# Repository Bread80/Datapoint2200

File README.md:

# Datapoint 2200 Schematics, Documents and PCB Recreations (WiP)

This is my project to transcribe the schematics for a Datapoint 2200 serial processor machine, reverse engineer them, and recreate the original hardware with added blinkenlights.

The repository contains schematics, PCB layout files, documents and software relevant to the 2200.

The schematics are in Kicad 5 format (at least until I make my peace with the UI in newer versions). To open them you may need to import the symbol library in Datapoint2200.lib and the Datapoint2200.pretty folder.

NOTES:
* These documents are still a work in progress.
* Schematics have not been double checked or verified against original hardware.
* On the original schematics some of the connector pinouts are ambiguous. DO NOT rely on the data in this repository when working with original hardware.

## Files
Some of the included files/PDFs:
* 2200_Drawing_package.pdf - Original schematics and engineering drawings.
* 2200_Reference_Manual.pdf - The operating manual for the machine including the assembly instruction set.
* 2200_Programmers_Man_Aug71.pdf - The processor instruction set, description of the standard libraries and operating instructions for the operating system, editor and assembler. Also contains a source code listing of the operating system software (but not the libraries, assembler or editor).
* 1405_Shift_Memory.pdf - Datasheet for the shift memory used in processor and video display.
* 74LS189_FairchildSemiconductor.pdf - Datasheet for the memory ICs used to implement the processor stack. (Which actually used very similiar 7489 ICs. The recreation has been designed to be able to use either).
* 1982_Standard_Microsystems.pdf - A datasheet catalogue which includes that for a character ROM compatible with one of those used in the video display, including character bitmaps.
* Datapoint2200.lib and .dcm - Kicab custom symbols (for Kicad 5).
* InstructionSet.txt - The instruction sets for both versions of the 2200 and the (very similar) Intel 8008.
* InstructionSet.xlsx - Spreadsheet version of the instruction sets (2200 and 8008) including comparisons against the Z80/8080.

## Folders/Boards
Schematics for each board are in their own folder.

The following lists the key boards of the Datapoint 2200 and the current status of each board.

### Board A1: Power Supply, Regulator
Status: Not transcribed.

### Board A2: Modulator
Modulator for the tape drives

Status: Not transcribed yet.

### Board A3: Demodulator
Demodulator for the tape drives

Status: Not transcribed yet.

### Board A4: Decoder
The system sequencer and output port/command decoder.

The schematic is split into the following files and functional units:
* Scheduler: Contains the system clock and gneerates signals to control the processort and machine as a whole.
* IODecoder: Decodes output port (command) addresses into individual signal lines.
* Speaker_Tape: Generates sound to the speaker (beeps and clicks), and houses some gates spilled over from the tape drive boards.

Status: A first revision board has been manufactured and works but has a couple of largely cosmetic issues, the worst of which is an incorrect footprint for the wide-body TTL chips. The PCB currently in the repository is the proposed next revision but which has not been tested - I'll have it manufactured when I know it is driving the rest of the system correctly.

### Board A5: Processor
---
The processor itself. The schematic is divided up as follows:
* AddressRegister: The address register (counter).
* AddrRegAndStackControl: Controls reading data into the address register and program counter, incrementing the program counter, and the stack.
* ALU: The ALU and carry flag.
* ARegister: The A register and I/O bus.
* Flags: The flags (other than carry) and conditional jump/call/return handling.
* InstrDecdoing: Instruction decoding.
* IRegister: The instruction register and register decoding.
* Processor: The main overview.
* Registers1: The H and L registers and data bus logic.
* Registers2: The B, C, D and E registers.
* Stack: The stack and stack pointer, and memory card selection.
* Timing: Fetch-execute cycle, memory word sync, HALTing and running, clocking and miscellaneous.

Status: The design has been tested in a logic emulator and appears to function correctly. A PCB layout has been made up and I'm currently adding LEDs (and establishing which signals should have LEDs) before sending the board for production.

### Board A6: Keyboard
---
Houses the keyswitches and multiplexing circuitry.

Status: Transcribed but not checked.

### Board A7: Deflection Amplifier
---
This board houses the circuitry for driving the CRT, and also some TTL logic spilled over from the Display Control board.

Status: The TTL circuits have been transcribed. I'm proposing to replace the CRT circuitry with something capable of driving a suitable modern display (ie. something microcontroller based).

### Board A8: Display Control
The 'video card'. Contains video memory, character generator and display driver. The board also controls the reading of data from the keyboard.

The schematic is divided as follows
* Input: I/O decoder for the display and keyboard (they use the same port address) and controls the latching of video data (control register, horizontal and vertical position and data).
* Memory: Video memory (using 1405 shift registers).
* Pixel Gen: Pixel clock, 'diddle scanning' (row and column wthin each character), characters ROMs and cursor generation.
* RowColumnSync: Row and column scanning and latches, and syncing the two for writing video data to memory.
* ClearAndOutput: Clearing memory for to-end-of-row, to-end-of-screen and clear-display functions. Outputting the status register (display busy and keyboard mounted switches).

Status: Transcribed and checked (but not validated).

### Board A9: Keyboard Logic
Contains the logic for scanning the keyboard, latching returned keypresses, and outputting characted codes in ASCII.

Contains the following modules:
* Reboot: Drives the processor after rebooting to load the boot data from a tape drive.
* ReadControl: Controls the processor's input bus. The board either outputs data from the keyboard itself or the bus buffers(probably).
* 'Sheet1': The main keyboard scanning and latching circuit. This name is probably not optimal.
* Shift: A circuit spilled opver from 'Sheet1' which controls 'shifting' of ASCII codes.
* BusBuffers: Comparators to boost the signals from the external bus and forward them to the processor's input bus.
* RunSwitch: A small circuit to latch the state of the Run switch.

Status: Transcribed and checked but not validated.

### Boards A11 to A14: Memory cards
Houses the Intel 1405 shift memories ICs used by the processor and related row and column decoders.

Status: Transcribed and first revision boards manufactured. The recreated PCBs include solder links to enable the memory to be operated at TTL voltage levels.
Note: The board has not been tested with actual 1405 chips.
Note: The 1405 ICs require a lot of power. The original PCBs are heavily engineered to be able to supply this power, and include a pair of bus bars for power distribution. The recreated PCBs have not been engineered to the same standards and shift should *not* be used with shift memories.

### Board A17: Motherboard
The 'backplane' into which many of the above boards slot (A1 to A9 except A6) or connect.

Status: Not transcribed yet

(Other board numbers are for smaller boards such as those in the tape machines, speaker mountings etc).

## Other Repository Contents
* Egde56: A test for for attaching to an edge connector.
* Software: A transcription and binaries for the operating system software listed in the Programmers Manual.

## Design Standards
These are mainly notes for myself to keep things consistent between boards.
  
Components:
  LEDs, side facing: Datapoint2200:LED_Dialight_597_xxxx_407F_SMT_RA_3mmx2mmx1mm (custom component and footprint in Datapoint2200 library)

Footprints:
Decoupling capacitors: Capacitor_THT:C_Disc_D7.0mm_W2.5mm_P5.00mm
Resistors (through hole): Resistor_THT:R_Axial_DIN0207_L6.3mm_D2.5mm_P10.16mm_Horizontal
Resistors (surface mount): 
  Decoder uses 0805: Resistor_SMD:R_0805_2012Metric_Pad1.20x1.40mm_HandSolder
  (other boards will vary!)
Mounting holes: MountingHole:MountingHole_3.2mm_M3
  Holes positioned 7x 25mils from board edges
Buttons (side mounted): Button_Switch_THT:SW_Tactile_SPST_Angled_PTS645Vx58-2LFS (exact model to be clarified)

Silkscreen:
All silkscreen placed on a 25mil (0.6250mm) grid
Section titles font size: W1.5 H1.5 Thickness: .25
Text for ICs:
  Top left: chip code (e.g. 7493), stated with original 74 series (no LS, HCT etc)
  Top right: reference code (e.g Z19)
  Below: chip description, centred. Use summary from datasheet where possible
Text for edge connector pins:
  Left (right on reverse) aligned to edge connector
  Use a < or > at connector end to indicate signal direction
  Positioned 50mil (2x0.6350mm) from connector pad
Edge connector pin numbers:
  Label first and last pin on each side.
  Font size: H1.5 H1.5 Thickness: 0.25
  Position: centred aligned
    8x 25mil horizontally from edge of connector pads
	4x 25mil vertically from centre of first pad
Board identifier (e.g. A4)
  Font size: H2 W2 Thickness: 0.35, orientation 90 degrees (i.e. from bottom to top) (Orientation valid for 'main' PCBs)
  Positioning: Centre aligned, 6x 25mils from board edge, 6x 25mils from edge of edge connector
Lines:
  Section separators: 0.5mm width
  Sub-section separators: 0.12mm width

*74x00	4	quad 2-input NAND gate			14	SN74LS00
*74x02	4	quad 2-input NOR gate			14	SN74LS02
*74x03	4	quad 2-input NAND gate		open-collector	14	SN74LS03
*74x04	6	hex inverter gate			14	SN74LS04
*74x05	6	hex inverter gate		open-collector	14	SN74LS05
**74x06	6	hex inverter gate		open-collector 30 V / 40 mA	14
*74x08	4	quad 2-input AND gate			14	SN74LS08
*74x10	3	triple 3-input NAND gate			14	SN74LS10
*74x20	2	dual 4-input NAND gate			14	SN74LS20
*74x30	1	single 8-input NAND gate			14	SN74LS30
**74x37	4	quad 2-input NAND gate		driver NO=30	14	SN74LS37
**74x40	2	dual 4-input NAND gate		driver NO=30	14	SN74LS40
*74x42	1	BCD to decimal decoder			16	SN74LS42
*74x73	2	dual J-K flip-flop, asynchronous clear			14	SN54LS73A
*74x74	2	dual D positive edge triggered flip-flop, asynchronous preset and clear			14	SN74LS74A
*74x85	1	4-bit magnitude comparator			16	SN74LS85
*74x89	1	64-bit RAM (16x4), 4 data inputs, 4 inverted data outputs		open-collector	16	SN7489
*74x95	1	4-bit shift register, parallel in, parallel out, serial input; different pinout for 74L95			14
*74x151	1	8-line to 1-line data selector/multiplexer			16	SN74151A
*74x153	2	dual 4-line to 1-line data selector/multiplexer, non-inverting outputs			16	SN74153
*74x164	1	8-bit serial-in parallel-out (SIPO) shift register, asynchronous clear, not output latch			14	SN74164
*74x193	1	synchronous presettable up/down 4-bit binary counter, clear			16	SN74193

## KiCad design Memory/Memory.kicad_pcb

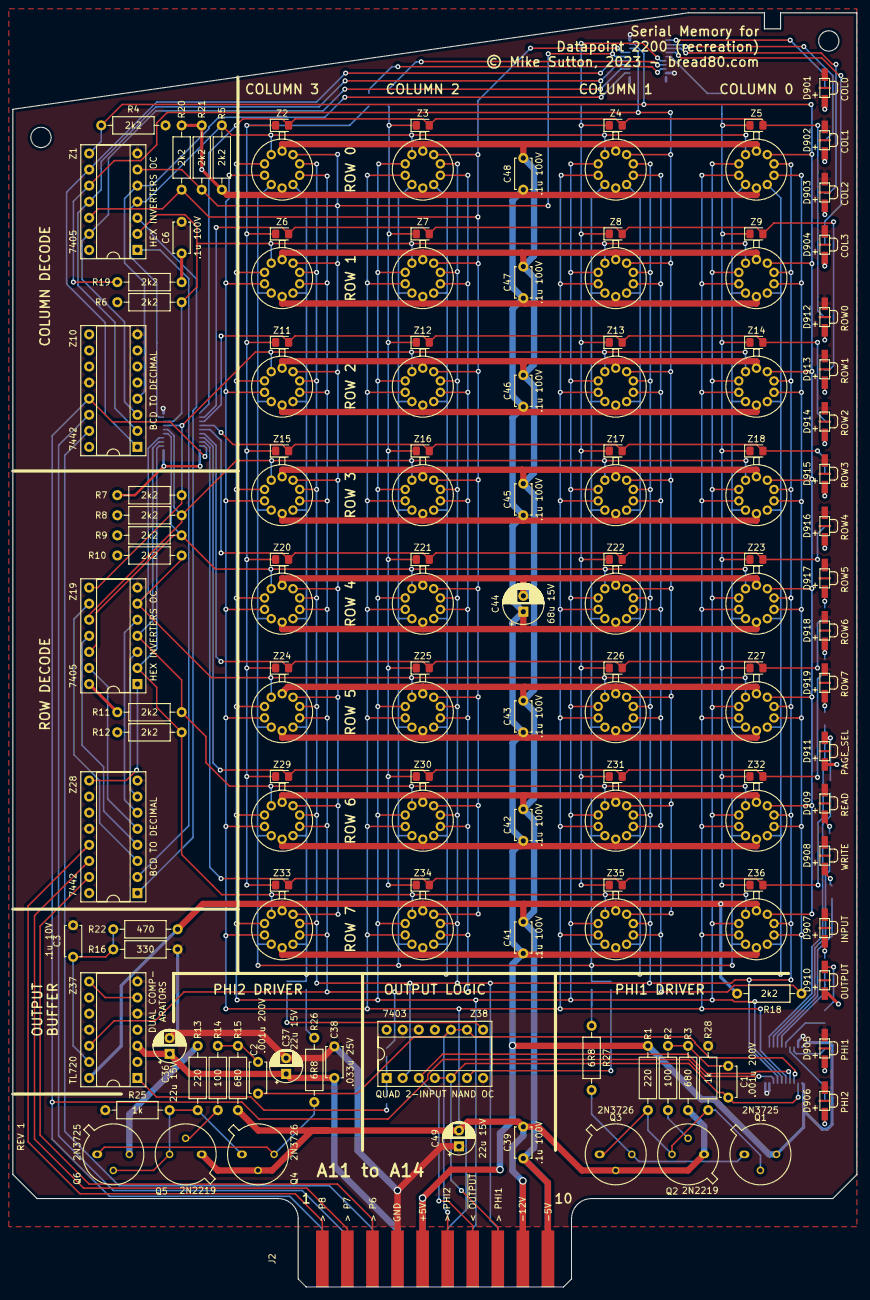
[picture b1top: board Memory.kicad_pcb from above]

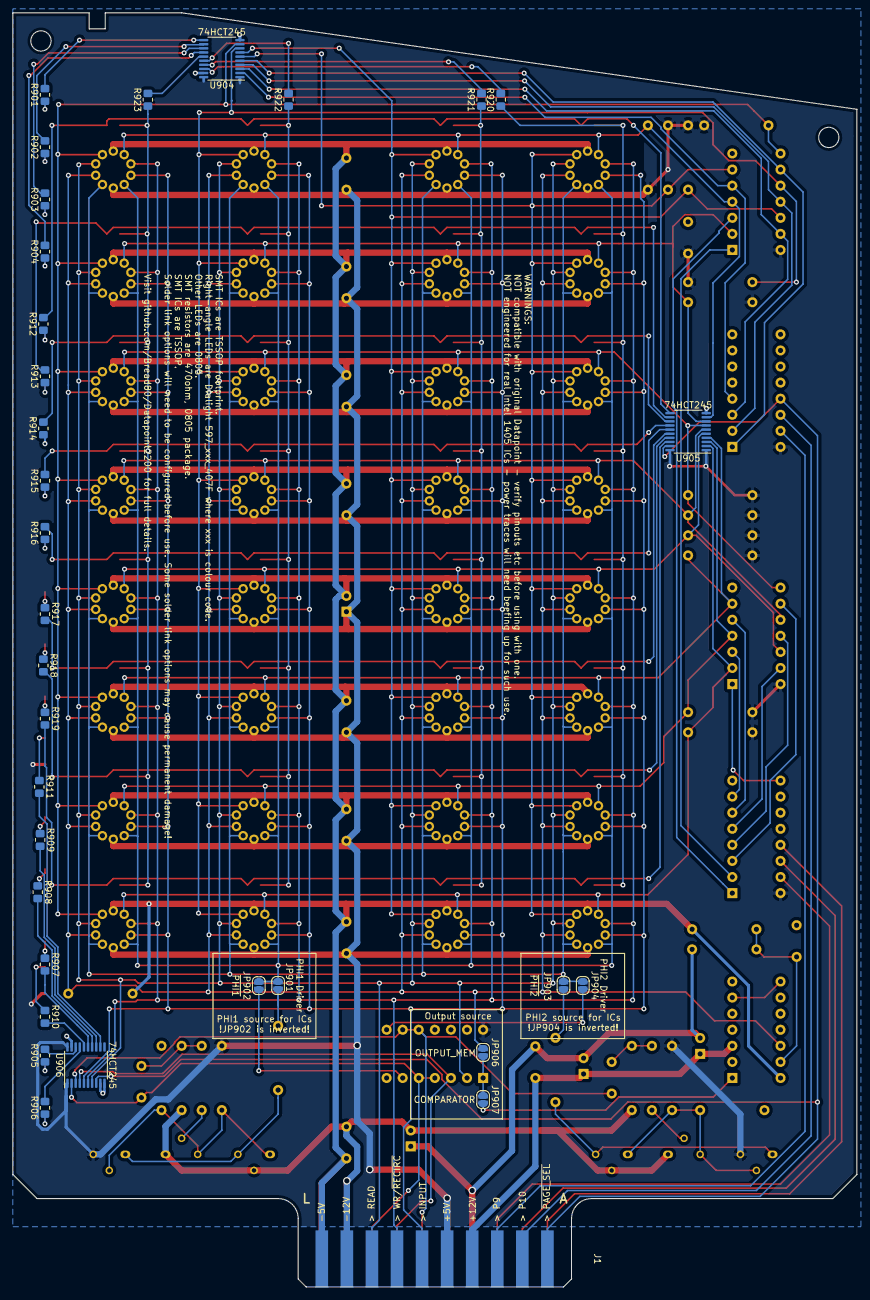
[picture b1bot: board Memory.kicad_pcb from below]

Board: 2 copper layers, 133.3 x 201.3 mm, 173 parts (33 on the bottom side), 106 nets.

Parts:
C1, C2: .001u 200V; C_Disc_D4.7mm_W2.5mm_P5.00mm
C3: .1u 10V; C_Disc_D4.7mm_W2.5mm_P5.00mm
C6, C39, C41, C42, C43, C45, C46, C47, C48: .1u 100V; C_Disc_D4.7mm_W2.5mm_P5.00mm
C36, C37, C49: 22u 15V; CP_Radial_D5.0mm_P2.50mm
C38: .033u 25V; C_Disc_D4.7mm_W2.5mm_P5.00mm
C44: 68u 15V; CP_Radial_D6.3mm_P2.50mm
D901: COL0; LED_Dialight_597_xxxx_407F_SMT_RA_3mmx2mmx1mm
D902: COL1; LED_Dialight_597_xxxx_407F_SMT_RA_3mmx2mmx1mm
D903: COL2; LED_Dialight_597_xxxx_407F_SMT_RA_3mmx2mmx1mm
D904: COL3; LED_Dialight_597_xxxx_407F_SMT_RA_3mmx2mmx1mm
D905: PHI1; LED_Dialight_597_xxxx_407F_SMT_RA_3mmx2mmx1mm
D906: PHI2; LED_Dialight_597_xxxx_407F_SMT_RA_3mmx2mmx1mm
D907: INPUT; LED_Dialight_597_xxxx_407F_SMT_RA_3mmx2mmx1mm
D908: WRITE; LED_Dialight_597_xxxx_407F_SMT_RA_3mmx2mmx1mm
D909: READ; LED_Dialight_597_xxxx_407F_SMT_RA_3mmx2mmx1mm
D910: OUTPUT; LED_Dialight_597_xxxx_407F_SMT_RA_3mmx2mmx1mm
D911: PAGE_SEL; LED_Dialight_597_xxxx_407F_SMT_RA_3mmx2mmx1mm
D912: ROW0; LED_Dialight_597_xxxx_407F_SMT_RA_3mmx2mmx1mm
D913: ROW1; LED_Dialight_597_xxxx_407F_SMT_RA_3mmx2mmx1mm
D914: ROW2; LED_Dialight_597_xxxx_407F_SMT_RA_3mmx2mmx1mm
D915: ROW3; LED_Dialight_597_xxxx_407F_SMT_RA_3mmx2mmx1mm
D916: ROW4; LED_Dialight_597_xxxx_407F_SMT_RA_3mmx2mmx1mm
D917: ROW5; LED_Dialight_597_xxxx_407F_SMT_RA_3mmx2mmx1mm
D918: ROW6; LED_Dialight_597_xxxx_407F_SMT_RA_3mmx2mmx1mm
D919: ROW7; LED_Dialight_597_xxxx_407F_SMT_RA_3mmx2mmx1mm
D920: Z5; LED_0805_2012Metric_Pad1.15x1.40mm_HandSolder
D921: Z4; LED_0805_2012Metric_Pad1.15x1.40mm_HandSolder
D922: Z3; LED_0805_2012Metric_Pad1.15x1.40mm_HandSolder
D923: Z2; LED_0805_2012Metric_Pad1.15x1.40mm_HandSolder
D924: Z9; LED_0805_2012Metric_Pad1.15x1.40mm_HandSolder
D925: Z8; LED_0805_2012Metric_Pad1.15x1.40mm_HandSolder
D926: Z7; LED_0805_2012Metric_Pad1.15x1.40mm_HandSolder
D927: Z6; LED_0805_2012Metric_Pad1.15x1.40mm_HandSolder
D928: Z14; LED_0805_2012Metric_Pad1.15x1.40mm_HandSolder
D929: Z13; LED_0805_2012Metric_Pad1.15x1.40mm_HandSolder
D930: Z12; LED_0805_2012Metric_Pad1.15x1.40mm_HandSolder
D931: Z11; LED_0805_2012Metric_Pad1.15x1.40mm_HandSolder
D932: Z18; LED_0805_2012Metric_Pad1.15x1.40mm_HandSolder
D933: Z17; LED_0805_2012Metric_Pad1.15x1.40mm_HandSolder
D934: Z16; LED_0805_2012Metric_Pad1.15x1.40mm_HandSolder
D935: Z15; LED_0805_2012Metric_Pad1.15x1.40mm_HandSolder
D936: Z23; LED_0805_2012Metric_Pad1.15x1.40mm_HandSolder
D937: Z22; LED_0805_2012Metric_Pad1.15x1.40mm_HandSolder
D938: Z21; LED_0805_2012Metric_Pad1.15x1.40mm_HandSolder
D939: Z20; LED_0805_2012Metric_Pad1.15x1.40mm_HandSolder
D940: Z27; LED_0805_2012Metric_Pad1.15x1.40mm_HandSolder
D941: Z26; LED_0805_2012Metric_Pad1.15x1.40mm_HandSolder
D942: Z25; LED_0805_2012Metric_Pad1.15x1.40mm_HandSolder
D943: Z24; LED_0805_2012Metric_Pad1.15x1.40mm_HandSolder
D944: Z32; LED_0805_2012Metric_Pad1.15x1.40mm_HandSolder
D945: Z31; LED_0805_2012Metric_Pad1.15x1.40mm_HandSolder
D946: Z30; LED_0805_2012Metric_Pad1.15x1.40mm_HandSolder
D947: Z29; LED_0805_2012Metric_Pad1.15x1.40mm_HandSolder
D948: Z36; LED_0805_2012Metric_Pad1.15x1.40mm_HandSolder
D949: Z35; LED_0805_2012Metric_Pad1.15x1.40mm_HandSolder
D950: Z34; LED_0805_2012Metric_Pad1.15x1.40mm_HandSolder
D951: Z33; LED_0805_2012Metric_Pad1.15x1.40mm_HandSolder
H901, H902: MountingHole; MountingHole_3.2mm_M3
J1: Edge_Bottom; EdgeConn_10_Pin_Pitch_3.96mm
J2: Edge_Top; EdgeConn_10_Pin_Pitch_3.96mm
JP901: PHI1 Driver; SolderJumper-2_P1.3mm_Open_RoundedPad1.0x1.5mm
JP902: ~PHI1; SolderJumper-2_P1.3mm_Open_RoundedPad1.0x1.5mm
JP903: PHI2 Driver; SolderJumper-2_P1.3mm_Open_RoundedPad1.0x1.5mm
JP904: ~PHI2; SolderJumper-2_P1.3mm_Open_RoundedPad1.0x1.5mm
JP906: OUTPUT_MEM; SolderJumper-2_P1.3mm_Open_RoundedPad1.0x1.5mm
JP907: COMPARATOR; SolderJumper-2_P1.3mm_Open_RoundedPad1.0x1.5mm
Q1, Q6: 2N3725; TO-39-3
Q2, Q5: 2N2219; TO-39-3
Q3, Q4: 2N3726; TO-39-3
R1, R13: 220; R_Axial_DIN0207_L6.3mm_D2.5mm_P10.16mm_Horizontal
R2, R14: 100; R_Axial_DIN0207_L6.3mm_D2.5mm_P10.16mm_Horizontal
R3, R15: 680; R_Axial_DIN0207_L6.3mm_D2.5mm_P10.16mm_Horizontal
R4, R5, R6, R7, R8, R9, R10, R11, R12, R18, R19, R20, R21: 2k2; R_Axial_DIN0207_L6.3mm_D2.5mm_P10.16mm_Horizontal
R16: 330; R_Axial_DIN0207_L6.3mm_D2.5mm_P10.16mm_Horizontal
R22: 470; R_Axial_DIN0207_L6.3mm_D2.5mm_P10.16mm_Horizontal
R25, R28: 1k; R_Axial_DIN0207_L6.3mm_D2.5mm_P10.16mm_Horizontal
R26, R27: 6R8; R_Axial_DIN0207_L6.3mm_D2.5mm_P10.16mm_Horizontal
R901, R902, R903, R904, R905, R906, R907, R908, R909, R910, R911, R912, R913, R914, R915, R916, R917, R918, R919, R920, R921, R922, R923: 470R; R_0805_2012Metric_Pad1.20x1.40mm_HandSolder
U904, U905, U906: 74HCT245; TSSOP-20_4.4x6.5mm_P0.65mm
Z1, Z19: 7405; DIP-14_W7.62mm_Socket
Z2, Z3, Z4, Z5, Z6, Z7, Z8, Z9, Z11, Z12, Z13, Z14, Z15, Z16, Z17, Z18, Z20, Z21, Z22, Z23, Z24, Z25, Z26, Z27, Z29, Z30, Z31, Z32, Z33, Z34, Z35, Z36: 1405; TO-99-10
Z10, Z28: 7442; DIP-16_W7.62mm_Socket
Z37: TL720; DIP-14_W7.62mm_Socket
Z38: 7403; DIP-14_W7.62mm_Socket

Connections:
+5V: C6.1, C41.1, C42.1, C43.1, C44.1, C45.1, C46.1, C47.1, C48.1, D910.2, D911.2, J1.5, J2.5, Q1.3, Q6.3, R1.2, R4.1, R5.2, R6.2, R7.2, R8.2, R9.2, R10.2, R11.2, R12.2, R13.2, R19.1, R20.1, R21.1, U904.1, U904.20, U905.1, U905.20, U906.1, U906.20, Z1.14, Z2.5, Z3.5, Z4.5, Z5.5, Z6.5, Z7.5, Z8.5, Z9.5, Z10.16, Z11.5, Z12.5, Z13.5, Z14.5, Z15.5, Z16.5, Z17.5, Z18.5, Z19.14, Z20.5, Z21.5, Z22.5, Z23.5, Z24.5, Z25.5, Z26.5, Z27.5, Z28.16, Z29.5, Z30.5, Z31.5, Z32.5, Z33.5, Z34.5, Z35.5, Z36.5, Z38.14
+12V: C36.1, C37.1, C38.1, J1.4, Z37.3
-5V: C39.1, C41.2, C42.2, C43.2, C44.2, C45.2, C46.2, C47.2, C48.2, J1.10, J2.10, R18.1, R22.2, Z2.10, Z3.10, Z4.10, Z5.10, Z6.10, Z7.10, Z8.10, Z9.10, Z11.10, Z12.10, Z13.10, Z14.10, Z15.10, Z16.10, Z17.10, Z18.10, Z20.10, Z21.10, Z22.10, Z23.10, Z24.10, Z25.10, Z26.10, Z27.10, Z29.10, Z30.10, Z31.10, Z32.10, Z33.10, Z34.10, Z35.10, Z36.10, Z37.14
-12V: C39.2, C49.2, J1.9, J2.9, Q2.1, Q3.2, Q4.2, Q5.1, R3.1, R15.1
COL0: R4.2, U904.9, Z1.8, Z5.9, Z9.9, Z14.9, Z18.9, Z23.9, Z27.9, Z32.9, Z36.9
COL1: R19.2, U904.8, Z1.10, Z4.9, Z8.9, Z13.9, Z17.9, Z22.9, Z26.9, Z31.9, Z35.9
COL2: R20.2, U904.7, Z1.12, Z3.9, Z7.9, Z12.9, Z16.9, Z21.9, Z25.9, Z30.9, Z34.9
COL3: R21.2, U904.6, Z1.6, Z2.9, Z6.9, Z11.9, Z15.9, Z20.9, Z24.9, Z29.9, Z33.9
GND: C3.1, C6.2, C36.2, C37.2, C38.2, C49.1, D901.1, D902.1, D903.1, D904.1, D905.1, D906.1, D907.1, D908.1, D909.1, D912.1, D913.1, D914.1, D915.1, D916.1, D917.1, D918.1, D919.1, J2.4, R16.1, R25.1, R28.1, U904.10, U904.19, U905.10, U906.9, U906.10, U906.19, Z1.7, Z10.8, Z10.12, Z19.7, Z28.8, Z28.12, Z37.5, Z37.7, Z37.11, Z38.7, Z38.12, Z38.13
INPUT: J1.6, U906.5, Z2.3, Z3.3, Z4.3, Z5.3, Z6.3, Z7.3, Z8.3, Z9.3, Z11.3, Z12.3, Z13.3, Z14.3, Z15.3, Z16.3, Z17.3, Z18.3, Z20.3, Z21.3, Z22.3, Z23.3, Z24.3, Z25.3, Z26.3, Z27.3, Z29.3, Z30.3, Z31.3, Z32.3, Z33.3, Z34.3, Z35.3, Z36.3
unnamed: C1.1, R2.2, R3.2
unnamed: C2.1, R14.2, R15.2
unnamed: C3.2, R16.2, R22.1, Z37.13
unnamed: D901.2, R901.1
unnamed: D902.2, R902.1
unnamed: D903.2, R903.1
unnamed: D904.2, R904.1
unnamed: D905.2, R905.1
unnamed: D906.2, R906.1
unnamed: D907.2, R907.1
unnamed: D908.2, R908.1
unnamed: D909.2, R909.1
unnamed: D910.1, R910.1
unnamed: D911.1, R911.1
unnamed: D912.2, R912.1
unnamed: D913.2, R913.1
unnamed: D914.2, R914.1
unnamed: D915.2, R915.1
unnamed: D916.2, R916.1
unnamed: D917.2, R917.1
unnamed: D918.2, R918.1
unnamed: D919.2, R919.1
unnamed: JP901.1, R27.1
unnamed: JP902.2, Z38.6
unnamed: JP903.1, R26.1
unnamed: JP904.2, Z38.8
unnamed: JP906.1, JP907.1, Z38.1
unnamed: JP907.2, Z37.1
unnamed: Q1.1, Q3.3, R27.2
unnamed: Q1.2, Q2.3, Q3.1, R1.1, R28.2
unnamed: Q2.2, R2.1
unnamed: Q4.1, Q5.3, Q6.2, R13.1, R25.2
unnamed: Q4.3, Q6.1, R26.2
unnamed: Q5.2, R14.1
unnamed: R901.2, U904.11
unnamed: R902.2, U904.12
unnamed: R903.2, U904.13
unnamed: R904.2, U904.14
unnamed: R905.2, U906.18
unnamed: R906.2, U906.17
unnamed: R907.2, U906.15
unnamed: R908.2, U906.14
unnamed: R909.2, U906.13
unnamed: R910.2, U906.16
unnamed: R911.2, U906.12
unnamed: R920.2, U904.18
unnamed: R921.2, U904.17
unnamed: R922.2, U904.16
unnamed: R923.2, U904.15
unnamed: Z1.1, Z28.2
unnamed: Z1.3, Z28.1
unnamed: Z19.1, Z28.9
unnamed: Z19.3, Z28.7
unnamed: Z19.5, Z28.6
unnamed: Z19.9, Z28.3
unnamed: Z19.11, Z28.4
unnamed: Z19.13, Z28.5
unnamed: Z37.6, Z37.8
OUTPUT_MEM: JP906.2, R18.2, Z2.7, Z3.7, Z4.7, Z5.7, Z6.7, Z7.7, Z8.7, Z9.7, Z11.7, Z12.7, Z13.7, Z14.7, Z15.7, Z16.7, Z17.7, Z18.7, Z20.7, Z21.7, Z22.7, Z23.7, Z24.7, Z25.7, Z26.7, Z27.7, Z29.7, Z30.7, Z31.7, Z32.7, Z33.7, Z34.7, Z35.7, Z36.7, Z37.12
P6: J2.3, Z28.15
P7: J2.2, Z28.14
P8: J2.1, Z28.13
P9: J1.3, Z10.15
P10: J1.2, Z10.14
PHI1: C1.2, J2.8, U906.2, Z38.4, Z38.5
PHI1_MEM: JP901.2, JP902.1, Z2.4, Z3.4, Z4.4, Z5.4, Z6.4, Z7.4, Z8.4, Z9.4, Z11.4, Z12.4, Z13.4, Z14.4, Z15.4, Z16.4, Z17.4, Z18.4, Z20.4, Z21.4, Z22.4, Z23.4, Z24.4, Z25.4, Z26.4, Z27.4, Z29.4, Z30.4, Z31.4, Z32.4, Z33.4, Z34.4, Z35.4, Z36.4
PHI2: C2.2, J2.6, U906.3, Z38.9, Z38.10
PHI2_MEM: JP903.2, JP904.1, Z2.6, Z3.6, Z4.6, Z5.6, Z6.6, Z7.6, Z8.6, Z9.6, Z11.6, Z12.6, Z13.6, Z14.6, Z15.6, Z16.6, Z17.6, Z18.6, Z20.6, Z21.6, Z22.6, Z23.6, Z24.6, Z25.6, Z26.6, Z27.6, Z29.6, Z30.6, Z31.6, Z32.6, Z33.6, Z34.6, Z35.6, Z36.6
R0: D920.2, D921.2, D922.2, D923.2, R912.2, U905.11
R1: D924.2, D925.2, D926.2, D927.2, R913.2, U905.12
R2: D928.2, D929.2, D930.2, D931.2, R914.2, U905.13
R3: D932.2, D933.2, D934.2, D935.2, R915.2, U905.14
R4: D936.2, D937.2, D938.2, D939.2, R916.2, U905.15
R5: D940.2, D941.2, D942.2, D943.2, R917.2, U905.16
R6: D944.2, D945.2, D946.2, D947.2, R918.2, U905.17
R7: D948.2, D949.2, D950.2, D951.2, R919.2, U905.18
READ: J1.8, U906.7, Z2.8, Z3.8, Z4.8, Z5.8, Z6.8, Z7.8, Z8.8, Z9.8, Z11.8, Z12.8, Z13.8, Z14.8, Z15.8, Z16.8, Z17.8, Z18.8, Z20.8, Z21.8, Z22.8, Z23.8, Z24.8, Z25.8, Z26.8, Z27.8, Z29.8, Z30.8, Z31.8, Z32.8, Z33.8, Z34.8, Z35.8, Z36.8, Z38.2
ROW0: R5.1, U905.9, Z1.4, Z2.1, Z3.1, Z4.1, Z5.1
ROW1: R6.1, U905.8, Z1.2, Z6.1, Z7.1, Z8.1, Z9.1
ROW2: R7.1, U905.7, Z11.1, Z12.1, Z13.1, Z14.1, Z19.8
ROW3: R8.1, U905.6, Z15.1, Z16.1, Z17.1, Z18.1, Z19.10
ROW4: R9.1, U905.5, Z19.12, Z20.1, Z21.1, Z22.1, Z23.1
ROW5: R10.1, U905.4, Z19.6, Z24.1, Z25.1, Z26.1, Z27.1
ROW6: R11.1, U905.3, Z19.4, Z29.1, Z30.1, Z31.1, Z32.1
ROW7: R12.1, U905.2, Z19.2, Z33.1, Z34.1, Z35.1, Z36.1
WRITE_~RECIRCULATE: J1.7, U906.6, Z2.2, Z3.2, Z4.2, Z5.2, Z6.2, Z7.2, Z8.2, Z9.2, Z11.2, Z12.2, Z13.2, Z14.2, Z15.2, Z16.2, Z17.2, Z18.2, Z20.2, Z21.2, Z22.2, Z23.2, Z24.2, Z25.2, Z26.2, Z27.2, Z29.2, Z30.2, Z31.2, Z32.2, Z33.2, Z34.2, Z35.2, Z36.2
~C0: D920.1, D924.1, D928.1, D932.1, D936.1, D940.1, D944.1, D948.1, R923.1
~C1: D921.1, D925.1, D929.1, D933.1, D937.1, D941.1, D945.1, D949.1, R922.1
~C2: D922.1, D926.1, D930.1, D934.1, D938.1, D942.1, D946.1, D950.1, R921.1
~C3: D923.1, D927.1, D931.1, D935.1, D939.1, D943.1, D947.1, D951.1, R920.1
~COL0: U904.5, Z1.9, Z10.1
~COL1: U904.4, Z1.11, Z10.2
~COL2: U904.3, Z1.13, Z10.3
~COL3: U904.2, Z1.5, Z10.4
~OUTPUT: J2.7, U906.4, Z38.3
~PAGE_SELECT: J1.1, U905.19, U906.8, Z10.13

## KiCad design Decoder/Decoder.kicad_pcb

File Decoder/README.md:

Revision History===Change HistoryRev 1OriginalRevision 2Fixed footprints for Z14, Z21Beefed up connections to edge connector for +5V and GNDRenamed S0 to S3 LEDs as C0 to C3Swapped order of C0 to C3Added central mounting hole to provide extra physical supportSlightly repositioned sequencer LEDs due to central spacer, and for better groupingLED for DIV64_CLK LED now driven from S3 (DIV64_CLK requires a pull-up which is positioned on the processor board)

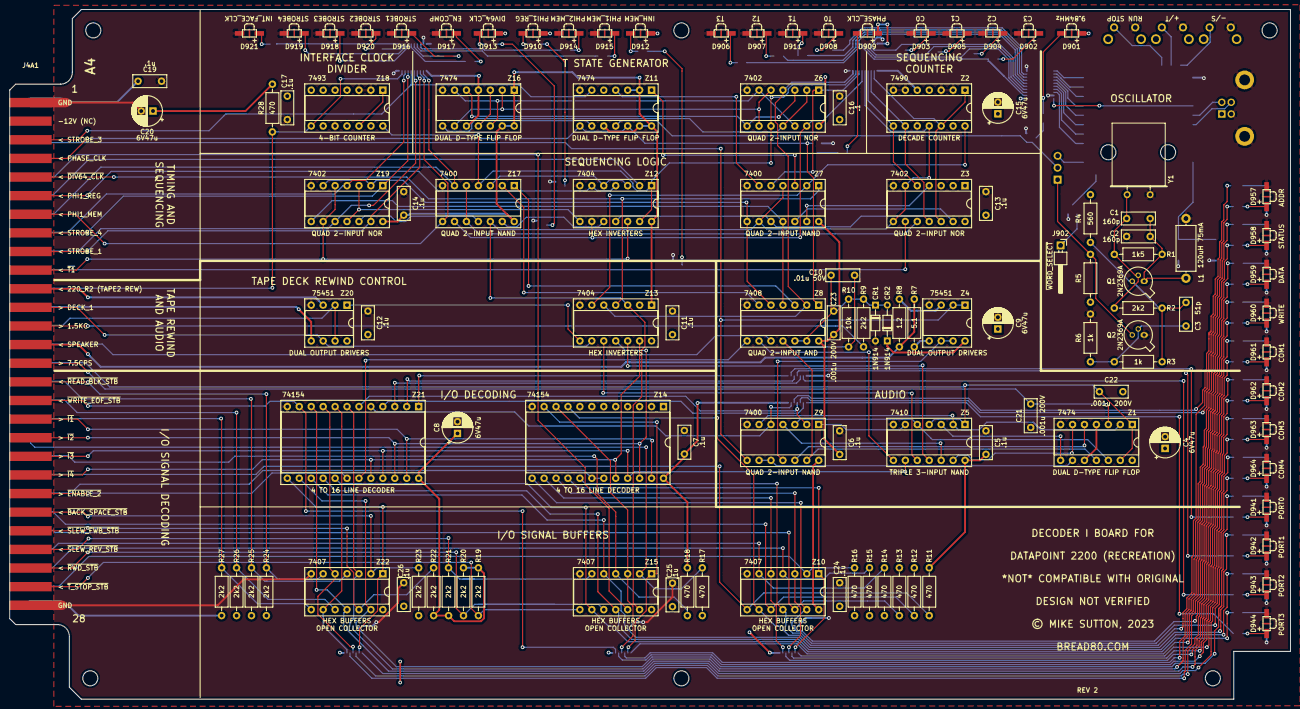
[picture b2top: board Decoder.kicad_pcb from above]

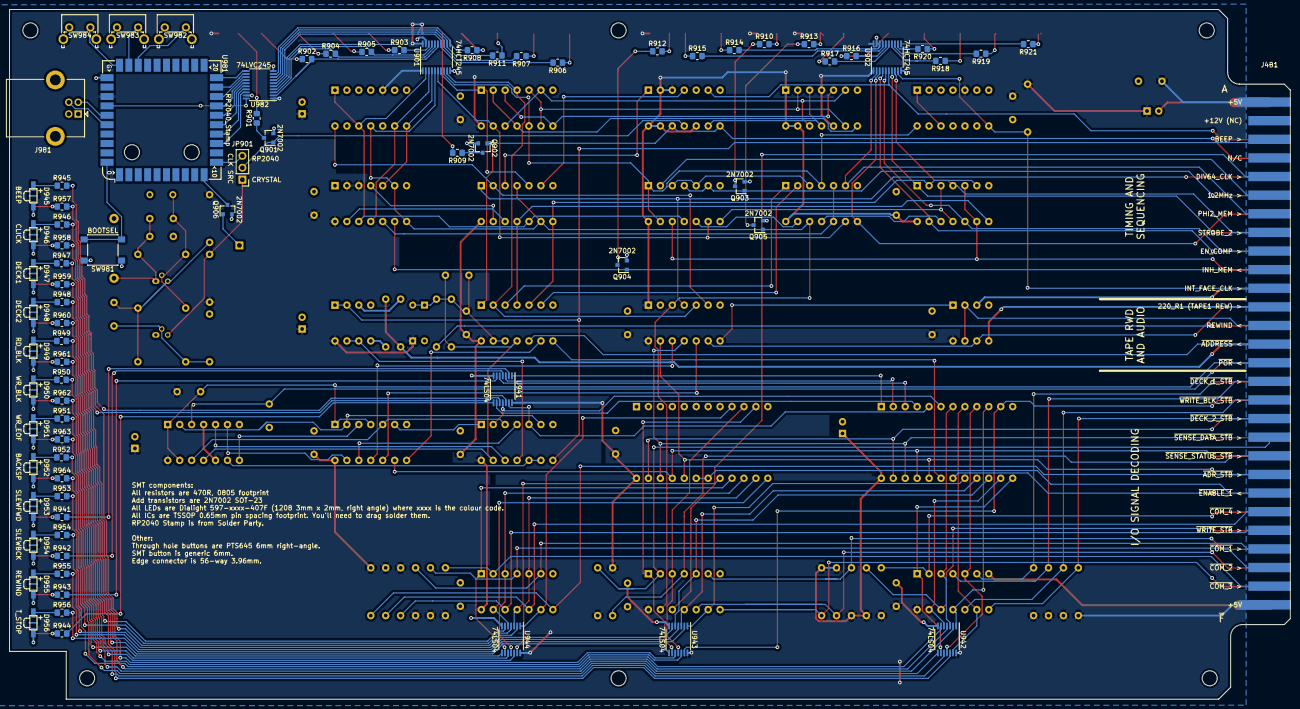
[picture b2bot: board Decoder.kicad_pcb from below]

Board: 2 copper layers, 272.4 x 146.7 mm, 202 parts (78 on the bottom side), 234 nets.

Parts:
C1, C2: 160p; C_Disc_D7.0mm_W2.5mm_P5.00mm
C3: 51p; C_Disc_D7.0mm_W2.5mm_P5.00mm
C4, C8, C9, C15, C20: 6V47u; CP_Radial_D6.3mm_P2.50mm
C5, C6, C7, C11, C12, C13, C14, C17, C19, C24, C25, C26: .1u; C_Disc_D7.0mm_W2.5mm_P5.00mm
C10: .01u 50V; C_Disc_D7.0mm_W2.5mm_P5.00mm
C16: .1; C_Disc_D7.0mm_W2.5mm_P5.00mm
C21, C22, C23: .001u 200V; C_Disc_D7.0mm_W2.5mm_P5.00mm
CR1, CR2: 1N914; D_DO-34_SOD68_P7.62mm_Horizontal
D901: 9.84MHz; LED_Dialight_597_xxxx_407F_SMT_RA_3mmx2mmx1mm
D902: C3; LED_Dialight_597_xxxx_407F_SMT_RA_3mmx2mmx1mm
D903: C0; LED_Dialight_597_xxxx_407F_SMT_RA_3mmx2mmx1mm
D904: C2; LED_Dialight_597_xxxx_407F_SMT_RA_3mmx2mmx1mm
D905: C1; LED_Dialight_597_xxxx_407F_SMT_RA_3mmx2mmx1mm
D906: T3; LED_Dialight_597_xxxx_407F_SMT_RA_3mmx2mmx1mm
D907: T2; LED_Dialight_597_xxxx_407F_SMT_RA_3mmx2mmx1mm
D908: T0; LED_Dialight_597_xxxx_407F_SMT_RA_3mmx2mmx1mm
D909: PHASE_CLK; LED_Dialight_597_xxxx_407F_SMT_RA_3mmx2mmx1mm
D910: PHI1_REG; LED_Dialight_597_xxxx_407F_SMT_RA_3mmx2mmx1mm
D911: T1; LED_Dialight_597_xxxx_407F_SMT_RA_3mmx2mmx1mm
D912: INH_MEM; LED_Dialight_597_xxxx_407F_SMT_RA_3mmx2mmx1mm
D913: DIV64_CLK; LED_Dialight_597_xxxx_407F_SMT_RA_3mmx2mmx1mm
D914: PHI2_MEM; LED_Dialight_597_xxxx_407F_SMT_RA_3mmx2mmx1mm
D915: PHI1_MEM; LED_Dialight_597_xxxx_407F_SMT_RA_3mmx2mmx1mm
D916: STROBE1; LED_Dialight_597_xxxx_407F_SMT_RA_3mmx2mmx1mm
D917: EN_COMP; LED_Dialight_597_xxxx_407F_SMT_RA_3mmx2mmx1mm
D918: STROBE3; LED_Dialight_597_xxxx_407F_SMT_RA_3mmx2mmx1mm
D919: STROBE4; LED_Dialight_597_xxxx_407F_SMT_RA_3mmx2mmx1mm
D920: STROBE2; LED_Dialight_597_xxxx_407F_SMT_RA_3mmx2mmx1mm
D921: INT_FACE_CLK; LED_Dialight_597_xxxx_407F_SMT_RA_3mmx2mmx1mm
D941: PORT0; LED_Dialight_597_xxxx_407F_SMT_RA_3mmx2mmx1mm
D942: PORT1; LED_Dialight_597_xxxx_407F_SMT_RA_3mmx2mmx1mm
D943: PORT2; LED_Dialight_597_xxxx_407F_SMT_RA_3mmx2mmx1mm
D944: PORT3; LED_Dialight_597_xxxx_407F_SMT_RA_3mmx2mmx1mm
D945: BEEP; LED_Dialight_597_xxxx_407F_SMT_RA_3mmx2mmx1mm
D946: CLICK; LED_Dialight_597_xxxx_407F_SMT_RA_3mmx2mmx1mm
D947: DECK1; LED_Dialight_597_xxxx_407F_SMT_RA_3mmx2mmx1mm
D948: DECK2; LED_Dialight_597_xxxx_407F_SMT_RA_3mmx2mmx1mm
D949: RD_BLK; LED_Dialight_597_xxxx_407F_SMT_RA_3mmx2mmx1mm
D950: WR_BLK; LED_Dialight_597_xxxx_407F_SMT_RA_3mmx2mmx1mm
D951: WR_EOF; LED_Dialight_597_xxxx_407F_SMT_RA_3mmx2mmx1mm
D952: BACKSP; LED_Dialight_597_xxxx_407F_SMT_RA_3mmx2mmx1mm
D953: SLEWFWD; LED_Dialight_597_xxxx_407F_SMT_RA_3mmx2mmx1mm
D954: SLEWBCK; LED_Dialight_597_xxxx_407F_SMT_RA_3mmx2mmx1mm
D955: REWIND; LED_Dialight_597_xxxx_407F_SMT_RA_3mmx2mmx1mm
D956: T_STOP; LED_Dialight_597_xxxx_407F_SMT_RA_3mmx2mmx1mm
D957: ADDR; LED_Dialight_597_xxxx_407F_SMT_RA_3mmx2mmx1mm
D958: STATUS; LED_Dialight_597_xxxx_407F_SMT_RA_3mmx2mmx1mm
D959: DATA; LED_Dialight_597_xxxx_407F_SMT_RA_3mmx2mmx1mm
D960: WRITE; LED_Dialight_597_xxxx_407F_SMT_RA_3mmx2mmx1mm
D961: COM1; LED_Dialight_597_xxxx_407F_SMT_RA_3mmx2mmx1mm
D962: COM2; LED_Dialight_597_xxxx_407F_SMT_RA_3mmx2mmx1mm
D963: COM3; LED_Dialight_597_xxxx_407F_SMT_RA_3mmx2mmx1mm
D964: COM4; LED_Dialight_597_xxxx_407F_SMT_RA_3mmx2mmx1mm
H901, H902, H903, H904, H905, H906, H907, H908: MountingHole; MountingHole_3.2mm_M3
J4A1: EdgeTop; EdgeConn_28_Pin_Pitch_3.96mm
J4B1: EdgeBottom; EdgeConn_28_Pin_Pitch_3.96mm
J902: ~WORD_SELECT; PinHeader_1x01_P2.54mm_Horizontal
J981: USB_B; USB_B_Lumberg_2411_02_Horizontal
JP901: CLK SRC; PinHeader_1x03_P2.54mm_Vertical
L1: 120uH 75mA; L_Axial_L9.5mm_D4.0mm_P12.70mm_Horizontal_Fastron_SMCC
Q1, Q2: 2N2369A; TO-18-3
Q901, Q902, Q903, Q904, Q905, Q906: 2N7002; SOT-23
R1: 1k5; R_Axial_DIN0207_L6.3mm_D2.5mm_P10.16mm_Horizontal
R2, R9, R19, R20, R21, R22, R23, R24, R25, R26, R27: 2k2; R_Axial_DIN0207_L6.3mm_D2.5mm_P10.16mm_Horizontal
R3, R5, R6: 1k; R_Axial_DIN0207_L6.3mm_D2.5mm_P10.16mm_Horizontal
R4: 560; R_Axial_DIN0207_L6.3mm_D2.5mm_P10.16mm_Horizontal
R7: 5.1; R_Axial_DIN0207_L6.3mm_D2.5mm_P10.16mm_Horizontal
R8: 1.2; R_Axial_DIN0207_L6.3mm_D2.5mm_P10.16mm_Horizontal
R10: 10k; R_Axial_DIN0207_L6.3mm_D2.5mm_P10.16mm_Horizontal
R11, R12, R13, R14, R15, R16, R17, R18, R28: 470; R_Axial_DIN0207_L6.3mm_D2.5mm_P10.16mm_Horizontal
R901, R902, R903, R904, R905, R906, R907, R908, R909, R910, R911, R912, R913, R914, R915, R916, R917, R918, R919, R920, R921, R941, R942, R943, R944, R945, R946, R947, R948, R949, R950, R951, R952, R953, R954, R955, R956, R957, R958, R959, R960, R961, R962, R963, R964: 470; R_0805_2012Metric_Pad1.20x1.40mm_HandSolder
SW981: BOOTSEL; SW_Push_1P1T_NO_6x6mm_H9.5mm
SW982: RUN STOP; SW_Tactile_SPST_Angled_PTS645Vx58-2LFS
SW983: +/T; SW_Tactile_SPST_Angled_PTS645Vx58-2LFS
SW984: -/S; SW_Tactile_SPST_Angled_PTS645Vx58-2LFS
U901, U902: 74HCT245; TSSOP-20_4.4x6.5mm_P0.65mm
U941, U942, U943, U944: 74LS04; TSSOP-14_4.4x5mm_P0.65mm
U981: RP2040_Stamp; RP2040_Stamp_SMD
U982: 74LVC245; TSSOP-20_4.4x6.5mm_P0.65mm
Y1: 9.8400MHz; Crystal_HC49-U_Horizontal
Z1, Z11, Z16: 7474; DIP-14_W7.62mm_Socket
Z2: 7490; DIP-14_W7.62mm_Socket
Z3, Z6, Z19: 7402; DIP-14_W7.62mm_Socket
Z4, Z20: 75451; DIP-8_W7.62mm_Socket
Z5: 7410; DIP-14_W7.62mm_Socket
Z7, Z9, Z17: 7400; DIP-14_W7.62mm_Socket
Z8: 7408; DIP-14_W7.62mm_Socket
Z10, Z15, Z22: 7407; DIP-14_W7.62mm_Socket
Z12, Z13: 7404; DIP-14_W7.62mm_Socket
Z14, Z21: 74154; DIP-24_W15.24mm_Socket
Z18: 7493; DIP-14_W7.62mm_Socket

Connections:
1.2MHz: J4B1.6, Z12.2
1.5KC: J4A1.13, R9.1
7.5CPS: C21.2, J4A1.15, Z1.3
9.84MHz: JP901.1, Q2.3, R5.1
220_R1: J4B1.12, Z20.5
220_R2: J4A1.11, Z20.3
+3V3: U981.34, U982.20
+5V: C4.1, C5.2, C6.2, C7.2, C8.1, C9.1, C11.2, C12.2, C13.1, C14.2, C15.1, C16.1, C17.1, C19.1, C20.1, C22.2, C23.1, C24.1, C25.1, C26.2, CR2.1, D901.2, D909.2, D910.2, D912.2, D913.2, J4B1.1, J4B1.28, R4.1, R5.2, R11.1, R12.1, R13.1, R14.1, R15.1, R16.1, R17.1, R18.1, R19.1, R20.1, R21.1, R22.1, R23.1, R24.1, R25.1, R26.1, R27.1, R28.2, U901.1, U901.20, U902.1, U902.20, U941.14, U942.14, U943.14, U944.14, U981.33, U982.1, Z1.4, Z1.10, Z1.14, Z2.5, Z3.2, Z3.3, Z3.14, Z4.8, Z5.14, Z6.14, Z7.14, Z8.14, Z9.14, Z10.14, Z11.2, Z11.3, Z11.10, Z11.13, Z11.14, Z12.14, Z13.1, Z13.14, Z14.24, Z15.14, Z16.1, Z16.4, Z16.10, Z16.13, Z16.14, Z17.14, Z18.5, Z19.14, Z20.8, Z21.24, Z22.14
/IODecoder/~BEEP: U941.13, Z9.5, Z21.5
/IODecoder/~CLICK: U941.11, Z9.2, Z21.6
/Scheduler/STEPS1TO8: Z8.6, Z17.2
/Scheduler/StampClock/C0: R903.2, U901.18, U982.5
/Scheduler/StampClock/C1: R905.2, U901.17, U982.4
/Scheduler/StampClock/C2: R904.2, U901.16, U982.3
/Scheduler/StampClock/C3: R902.2, U901.15, U982.2
/Scheduler/StampClock/T0: R908.2, U901.11, U982.9
/Scheduler/StampClock/T1: R911.2, U901.12, U982.8
/Scheduler/StampClock/T2: R907.2, U901.13, U982.7
/Scheduler/StampClock/T3: R906.2, U901.14, U982.6
/Scheduler/~C0: Z7.11, Z8.4, Z19.8
/Scheduler/~STEP8: Z17.11, Z19.12
/Scheduler/~STEP8or9_T2: Z7.6, Z11.4
/Scheduler/~T0: Z2.14, Z7.2, Z13.6
/Scheduler/~T3: Z12.8, Z19.3, Z19.11
/Speaker_Tape/SP1: R7.1, Z4.5
/Speaker_Tape/SP2: R8.1, Z4.3
BEEP: J4B1.3, Z4.1, Z4.2, Z9.8
C0: U901.2, Z2.1, Z2.12, Z3.12, Z7.10, Z12.11
C1: U901.3, Z2.9, Z3.11
C2: U901.4, Z2.8, Z3.5
C3: Q905.1, U901.5, Z2.11, Z3.6, Z3.8, Z7.4, Z7.9, Z13.3, Z15.13, Z17.12
DECK_1: J4A1.12, Z13.9, Z20.6
DIV64_CLK: J4B1.5, Z15.12
EN_COMP: J4B1.9, U902.5, Z19.10
GND: C2.2, C4.2, C5.1, C6.1, C7.1, C8.2, C9.2, C11.1, C12.1, C13.2, C14.1, C15.2, C16.2, C17.2, C19.2, C20.2, C21.1, C24.2, C25.2, C26.1, CR1.2, D902.1, D903.1, D904.1, D905.1, D906.1, D907.1, D908.1, D911.1, D914.1, D915.1, D916.1, D917.1, D918.1, D919.1, D920.1, D921.1, D941.1, D942.1, D943.1, D944.1, D945.1, D946.1, D947.1, D948.1, D949.1, D950.1, D951.1, D952.1, D953.1, D954.1, D955.1, D956.1, D957.1, D958.1, D959.1, D960.1, D961.1, D962.1, D963.1, D964.1, J4A1.1, J4A1.28, J981.4, J981.5, L1.2, Q2.1, Q901.2, Q902.2, Q903.2, Q904.2, Q905.2, Q906.2, R6.1, SW981.1, SW982.1, SW983.1, SW984.1, U901.10, U901.19, U902.10, U902.19, U941.7, U942.7, U943.7, U944.7, U981.31, U982.10, U982.19, Y1.1, Z1.7, Z2.2, Z2.3, Z2.6, Z2.7, Z2.10, Z3.7, Z4.4, Z5.7, Z6.7, Z7.7, Z8.7, Z9.7, Z10.7, Z11.7, Z12.7, Z13.7, Z14.12, Z15.7, Z16.7, Z17.7, Z18.2, Z18.3, Z18.10, Z19.7, Z20.4, Z21.12, Z22.7
I1: J4A1.18, Z14.23, Z21.23
I2: J4A1.19, Z13.11, Z14.22, Z21.22
I3: J4A1.20, Z5.9, Z14.21, Z21.21
I4: J4A1.21, Z13.13, Z14.20, Z21.20
INH_MEM: J4B1.10, Q904.1, Z3.9
INT_FACE_CLK: J4B1.11, R28.1, U902.9, Z18.8
unnamed: C1.1, Q1.2, R1.1, R2.2, Y1.2
unnamed: C1.2, C2.1, L1.1, Q1.1, R1.2
unnamed: C3.1, Q2.2, R3.1, R6.2
unnamed: C3.2, Q1.3, R2.1, R3.2, R4.2
unnamed: C10.1, R10.1, Z1.11, Z8.11, Z9.13
unnamed: C10.2, C23.2, CR1.1, CR2.2, R9.2, R10.2, Z8.12, Z8.13
unnamed: D901.1, R901.2
unnamed: D902.2, R902.1
unnamed: D903.2, R903.1
unnamed: D904.2, R904.1
unnamed: D905.2, R905.1
unnamed: D906.2, R906.1
unnamed: D907.2, R907.1
unnamed: D908.2, R908.1
unnamed: D909.1, R909.2
unnamed: D910.1, R910.2
unnamed: D911.2, R911.1
unnamed: D912.1, R912.2
unnamed: D913.1, R913.2
unnamed: D914.2, R914.1
unnamed: D915.2, R915.1
unnamed: D916.2, R916.1
unnamed: D917.2, R917.1
unnamed: D918.2, R918.1
unnamed: D919.2, R919.1
unnamed: D920.2, R920.1
unnamed: D921.2, R921.1
unnamed: D941.2, R941.1
unnamed: D942.2, R942.1
unnamed: D943.2, R943.1
unnamed: D944.2, R944.1
unnamed: D945.2, R945.1
unnamed: D946.2, R946.1
unnamed: D947.2, R947.1
unnamed: D948.2, R948.1
unnamed: D949.2, R949.1
unnamed: D950.2, R950.1
unnamed: D951.2, R951.1
unnamed: D952.2, R952.1
unnamed: D953.2, R953.1
unnamed: D954.2, R954.1
unnamed: D955.2, R955.1
unnamed: D956.2, R956.1
unnamed: D957.2, R957.1
unnamed: D958.2, R958.1
unnamed: D959.2, R959.1
unnamed: D960.2, R960.1
unnamed: D961.2, R961.1
unnamed: D962.2, R962.1
unnamed: D963.2, R963.1
unnamed: D964.2, R964.1
unnamed: J902.1, Q906.1
unnamed: J981.2, U981.35
unnamed: J981.3, U981.36
unnamed: Q901.3, R901.1
unnamed: Q902.3, R909.1
unnamed: Q903.3, R910.1
unnamed: Q904.3, R912.1
unnamed: Q905.3, R913.1
unnamed: R914.2, U902.18
unnamed: R915.2, U902.17
unnamed: R916.2, U902.16
unnamed: R917.2, U902.15
unnamed: R918.2, U902.14
unnamed: R919.2, U902.13
unnamed: R920.2, U902.12
unnamed: R921.2, U902.11
unnamed: R941.2, U941.2
unnamed: R942.2, U941.4
unnamed: R943.2, U941.6
unnamed: R944.2, U941.8
unnamed: R945.2, U941.12
unnamed: R946.2, U941.10
unnamed: R947.2, U942.4
unnamed: R948.2, U942.12
unnamed: R949.2, U942.10
unnamed: R950.2, U942.2
unnamed: R951.2, U943.12
unnamed: R952.2, U942.8
unnamed: R953.2, U942.6
unnamed: R954.2, U943.6
unnamed: R955.2, U943.4
unnamed: R956.2, U943.2
unnamed: R957.2, U944.2
unnamed: R958.2, U943.10
unnamed: R959.2, U943.8
unnamed: R960.2, U944.6
unnamed: R961.2, U944.12
unnamed: R962.2, U944.10
unnamed: R963.2, U944.8
unnamed: R964.2, U944.4
unnamed: SW981.2, U981.40
unnamed: SW982.2, U981.28
unnamed: SW983.2, U981.29
unnamed: SW984.2, U981.30
unnamed: U981.13, U982.18
unnamed: U981.14, U982.17
unnamed: U981.15, U982.16
unnamed: U981.16, U982.15
unnamed: U981.17, U982.14
unnamed: U981.18, U982.13
unnamed: U981.19, U982.12
unnamed: U981.20, U982.11
unnamed: Z1.2, Z5.2, Z9.6
unnamed: Z1.5, Z9.12
unnamed: Z1.6, Z5.13
unnamed: Z1.8, Z5.3
unnamed: Z1.9, Z9.9, Z9.10
unnamed: Z1.12, Z5.5, Z9.3
unnamed: Z3.4, Z7.13
unnamed: Z3.13, Z7.12
unnamed: Z4.6, Z4.7, Z9.11
unnamed: Z5.6, Z9.1
unnamed: Z5.8, Z8.9
unnamed: Z5.12, Z9.4
unnamed: Z7.3, Z11.1
unnamed: Z11.9, Z16.3, Z16.11
unnamed: Z12.3, Z12.5, Z17.3
unnamed: Z12.10, Z17.13
unnamed: Z13.8, Z20.1
unnamed: Z5.10, Z13.10
unnamed: Z5.11, Z13.12
unnamed: Z6.5, Z6.9, Z16.2, Z16.9
unnamed: Z6.3, Z6.8, Z16.5
unnamed: Z6.2, Z6.11, Z16.8
unnamed: Z6.6, Z6.12, Z16.6, Z16.12
unnamed: Z8.3, Z17.1
unnamed: Z3.10, Z17.5, Z17.10
unnamed: Z18.1, Z18.12
unnamed: Z8.8, Z21.19
PHASE_CLK: J4A1.4, Q902.1, Z8.1, Z11.8, Z11.12
PHI1_MEM: J4A1.7, U902.3, Z17.8
PHI1_REG: J4A1.6, Q903.1, Z12.4, Z12.6
PHI2_MEM: J4B1.7, U902.2, Z17.6
REWIND: J4B1.13, Z20.2, Z20.7
RP_CLK: JP901.3, U981.11
SPEAKER: J4A1.14, R7.2, R8.2
STROBE_1: J4A1.9, U902.4, Z19.13
STROBE_2: J4B1.8, U902.8, Z19.4
STROBE_3: J4A1.3, U902.6, Z11.6
STROBE_4: J4A1.8, U902.7, Z19.1
SYS_CLK: JP901.2, Q901.1, Z11.11
T0: U901.9, Z6.4, Z8.2, Z13.5
T1: U901.8, Z6.10, Z12.1, Z12.13, Z17.4, Z18.14
T2: U901.7, Z6.1, Z7.5
T3: U901.6, Z6.13, Z12.9, Z17.9
WORD_SELECT: Q906.3, U981.10
~ADDRESS: J4B1.14, Z8.10
~ADR: U944.1, Z10.9, Z14.9
~ADR_STB: J4B1.21, R11.2, Z10.8
~BACK_SPACE: U942.9, Z21.13, Z22.1
~BACK_SPACE_STB: J4A1.23, R23.2, Z22.2
~COM1: U944.13, Z10.5, Z14.14
~COM2: U944.11, Z10.3, Z14.15
~COM3: U944.9, Z10.1, Z14.16
~COM4: U944.3, Z10.11, Z14.17
~COM_1: J4B1.25, R14.2, Z10.6
~COM_2: J4B1.26, R15.2, Z10.4
~COM_3: J4B1.27, R16.2, Z10.2
~COM_4: J4B1.23, R12.2, Z10.10
~DECK_1: U942.3, Z21.7, Z22.3
~DECK_1_STB: J4B1.16, R25.2, Z22.4
~DECK_2: U942.13, Z21.8, Z22.9
~DECK_2_STB: J4B1.18, R27.2, Z22.8
~DIV64_CLK: J4A1.5, Z7.1, Z13.4
~ENABLE_1: J4B1.22, Z14.18, Z14.19
~ENABLE_2: J4A1.22, Z21.18
~POR: C22.1, J4B1.15, Z1.1, Z1.13, Z5.1, Z5.4
~PORT0: U941.1, Z21.1
~PORT1: U941.3, Z21.2
~PORT2: U941.5, Z21.3
~PORT3: U941.9, Z21.4
~READ_BLK: U942.11, Z21.9, Z22.5
~READ_BLK_STB: J4A1.16, R24.2, Z22.6
~RWD: U943.3, Z15.11, Z21.16
~RWD_STB: J4A1.26, R20.2, Z15.10
~SENSE_DATA: U943.9, Z14.11, Z15.1
~SENSE_DATA_STB: J4B1.19, R17.2, Z15.2
~SENSE_STATUS: U943.11, Z14.10, Z15.3
~SENSE_STATUS_STB: J4B1.20, R18.2, Z15.4
~SLEW_FWB: U942.5, Z21.14, Z22.13
~SLEW_FWB_STB: J4A1.24, R22.2, Z22.12
~SLEW_REV: U943.5, Z15.5, Z21.15
~SLEW_REV_STB: J4A1.25, R21.2, Z15.6
~STEP9: Z7.8, Z8.5, Z19.2, Z19.6
~T1: J4A1.10, Z12.12, Z19.5, Z19.9
~T_STOP: U943.1, Z15.9, Z21.17
~T_STOP_STB: J4A1.27, R19.2, Z15.8
~WRITE: U944.5, Z10.13, Z14.13
~WRITE_BLK: U942.1, Z21.10, Z22.11
~WRITE_BLK_STB: J4B1.17, R26.2, Z22.10
~WRITE_EOF_STB: J4A1.17, U943.13, Z21.11
~WRITE_STB: J4B1.24, R13.2, Z10.12

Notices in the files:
Decoder/Decoder.kicad_pcb:
© MIKE SUTTON, 2023
Memory/Memory.kicad_pcb:
© Mike Sutton, 2023 - bread80.com
